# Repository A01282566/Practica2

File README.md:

# Practice 2. Developiong the PCB (Layout)

## Objectives

Develop the connection diagrams (layout) from the schematic diagram.

## Introduction

Microcontrollers are all around  he world. Each day, Microcontrollers, are more present in the many aspects of our lives: in our work, inside our houses, and in more. We can find them controlling small devices like cellphones, microwaves, washing machines, and televisions.

A microcontroller is one device or chip that is used to govern one or more processes. For example, the controller that regulates the room temperature of an air conditioner; it has a sensor that continuously measures the internal temperature and, when the preset limits are exceeded, it generates the necessary signals to adjust the temperature.

## State of the Art

### The practices and the PIC microcontroller

The main objective of this practices is to provide students the foundation to fully understand the operation of the PIC18F45K50 microcontroller. This will be achieved through 11 documents that will guide the reader to create their own electronic card or Printed Circuit Board (PCB) and to be able to program it; in order to, execute different functions.

The advantages of ta PIC microcontroller to others on the market, which is why it will be used throughout this manual, are as follows:

- Easy to operate.
- There is enough documentation to work with it and it’s easy to obtain it.
- The price is comparatively lower than its competitors.
- It has a high operating speed.
- Development tools are cheap and easy to use.
- There are a variety of hardware that can record, erase and check the behavior of PIC.
- Once you learn to handle a PIC, it will easier to handle any other models of microcontrollers.

### KiCad EDA Software

KiCad is an open source software suite for Electronic Design Automation (EDA). The programs handle Schematic Capture,
and PCB Layout with Gerber output. The suite runs on Windows, Linux and macOS and is licensed under GNU GPL v3. The
first release date was in 1992 by its original author, Jean-Pierre Charras, but is now currently under development by
the KiCad Developers Team. 

## Results

In this section, you must report the outcomes of the laboratory activities.

### Follow the next 'Project Configuration' Steps

1. In  the  same  project  from  practice  1,  click  on  the  icon ‘Assign PCB footprints to schematic symbols’.  By  doing  so,  you  will  be  able  to  watch  the  footprints associations in a list format. ***NOTE:*** *If a ***‘Confirmation’*** window pops to reassign all the components to a new library format, click ‘No.’*

2. Now it is time to add the corresponding libraries to the Cvpcbprogram.   Download from [here](./modules)  the modules   needed   for   the   project.   Click   on Preferences→Manage Footprint Libraries...and  in this  way  you  will  be  able  to  add  the  modules  from the folder  named  ‘modules.’  Click  on  ‘Project  Specific Libraries...’  tab,  then  click  on  the  button  ‘Browse Libraries...’ and search for the folder  where  you  save the modules. Select all the files and click ‘OK.’Fig.  1 shows the result of the added modules. NOTE:Your KiCad EDA Software must be in english to add the modules.

3. Once  that  is  done,  you  must  associate  the  list  of components  with  its  respective  footprint using Table  I for  guidance.  Be  sure  to  activate  the  option  ‘Filter footprints  list  by  library’ from  the Cvpcbtoolbar. To associate  the  components  showed  in  the middle  column,  double  click  with  their  corresponding footprint from the right column. ***NOTE:*** *Search  all  the  footprints  in  the*  ***‘user’*** *and * 
***‘discrete’*** * added libraries that should be found at the end of the list.*

4. Save   your modifications  by  clicking  **‘Apply,  Save Schematic & Continue,’ and then click ‘OK.’**
5. After that, you may close the Cvpcband go back to the EESchema (Schematic  Editor.)  Save  your  project  by clicking   on File→Save.   Close   the   editor   of   the Schematic and switch back to the **‘Project Manager.’**

6. Once you have the design of the circuit on the schematic, it is time to generate the **‘layout’** of our PCB  using the Netlist  file. On  the Project  Manager program  from KiCad, click on the icon **‘PCB layout editor’** . A new window will appear from the PCBNew. Click **‘Yes’** in the confirmation window.
7. On  the  toolbar  menu  from  the PCBNew click  on  the **‘Page  Settings  for  paper  size  and  texts’**
and modify the size settings to **‘USLetter 8.5x11in.’**

8. After  that,  it  will be  time  to  focus  more  on  design concepts.  You  may  do  so  by  opening  the
menu  of **‘Setup→Design Rules...’**. On   it,   some   final   design characteristics will appear with many millimeter values. Between   them,   you   should   find  the  **‘Clearance’** specification  which  is  the  smallest  spaces  that  it  must exist  between  the tracks  on the  PCB.  You  shall  set the value of this cell to 0.508 mm (0.020 inches.) Next, we set  a  value  of 1.200  mm  (0.047244 inches)on the  cell of **‘Track Width.’** 

9. Switch now to the ‘Global Design Rules’ tab and write, if needed, the minimum values for each an every one of the parameters on the ‘Minimum Allowed Values’ box. Click ‘OK.’

10. Time  to  import  the  Netlist  file.  Go  to  the  toolbar ‘Tools→Update  PCB  from  Schematic...’  and  then click on ‘Update  PCB.’ When  you  close  the  window all the components will appear on the screen.

11.Check in the ‘Layers Manager’ window (located at the right  part  of  your  screen) that all  the needed  boxes  are
checked, as shown:

11.Check in the ‘Layers Manager’ window (located at the right  part  of  your  screen) that all  the needed  boxes  are checke

12. Now you  have  to  define  the  limits  of  the  PCB.  First, highlight  the  ‘Edge.Cuts’  layer.  Then,  select  the  ‘Add  graphic lines’ tool and began to trace the original measures of your copper board (15x20 cm.) You must also define the  cutting  area;  do  not  forget  to  add  a  2.5  cm  margin around the board. To measure the lines, you can use the ‘Add dimension’ tool located on the right.

13. It is your turn to move all the components in the circuit in  order  to  avoid  any  track  intersection  inside  the working   area.   You   can   move   the   components   by positioning your mouse pointer above it and pressing the key [G]. All the components are connected to each other by a group of wires called ratsnest. Make sure that the icon  of  **‘Hide  board  ratsnest’** located  in  the toolbar of the left is highlighted.

14. Now you must link all the connections of you PCB. But before  that,  you  must  change  the  drawing  option  from the right toolbar from ‘Edge.Cuts’ to ‘B.Cu (PgDn)’ (B->Bottom, Cu->Copper.).

15. Start to connect your tracks to each and every one pin on the schematic by using the icon ‘Route Tracks’. Trace  all  the  routes  for  each  net  or  connection  in  your PCB design.

16. Once  your  are  done,  save  your  layout  File->Save  or using the command [Ctrl + S].

17. Your board must look like:

### Report
For this practice, modify only the Conclusion section. Commit an push the changes on the fork of this repository and add
upload the link on Canvas.

### File uploads
Commit and push the files with extensions .pro and .kicad_pcb created once you completed all the steps of the document in the repository.

### Demonstration
Screenshot the image of the complete schematic and upload it at the repository.

## Conclusion

In conclusion it can be said that with KidCad not only we can draw the schematic but also do the PCB layout of it. One problem that I had was that I couldn't draw the green connection lines at fisrt, but after I told my professor about it, we resolved it during tutoring. Also, one thing very difficult for me was to understand the white webs that are supposed to guide the conecctions, but later I realized that it was because I needed to rotate certain elements in order to see the lines clearer, as they were very confusing.
So, with this practice I discovered that those web lines are very helpful, so you don't have to be looking at the schematic all the time. And, I learned how to draw the copper lines to delimitate the area of the PCB.

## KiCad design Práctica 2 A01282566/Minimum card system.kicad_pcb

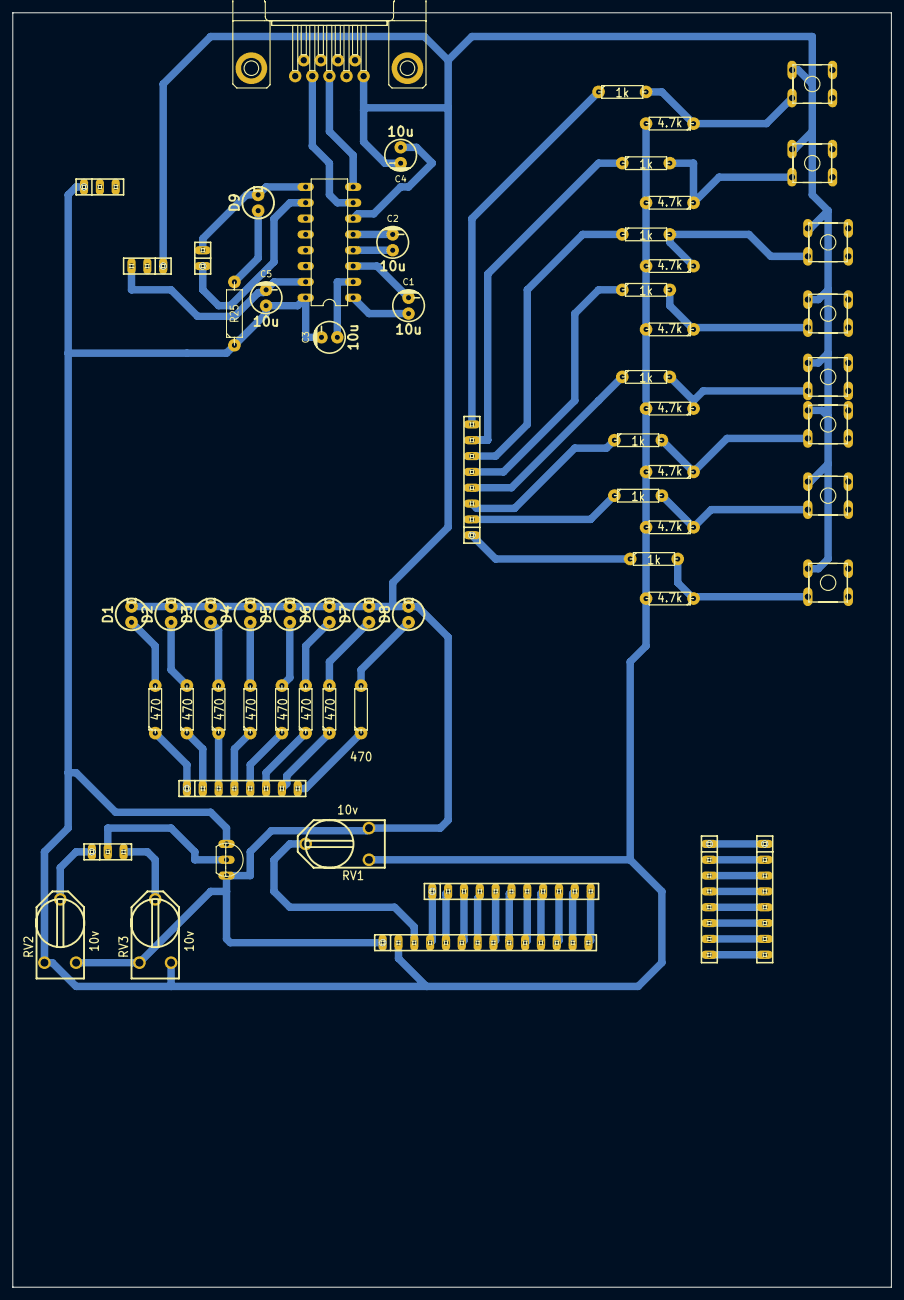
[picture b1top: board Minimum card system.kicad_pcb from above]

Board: 2 copper layers, 141.0 x 204.5 mm, 63 parts (0 on the bottom side), 68 nets.

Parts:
C1, C2, C3, C4, C5: 10u; Capacitor_elect
D1, D2, D3, D4, D5, D6, D7, D8, D9: LED; Led
JP1, JP2, JP7: PINHD-1X3; pinhead-1X03
JP3: PINHD-1X14; pinhead-1X14
JP4, JP5, JP8, JP9: PINHD-1X8; pinhead-1X08
JP6: PINHD-1X11; pinhead-1X11
JP10: PINHD-1X2; pinhead-1X02
R1, R2, R3, R4, R5, R6, R7, R8: 470; Resistor
R9, R10, R11, R12, R13, R14, R15, R16: 1k; Resistor
R17, R18, R19, R20, R21, R22, R23, R24: 4.7k; Resistor
R25: 470; Resistor_large
RV1, RV2, RV3: 10v; RV2X4
S1, S2, S3, S4, S5, S6, S7, S8: DTS-6
U1: MCP9700A
U2: MAX232; Maxim232
X1: F09HP; Conector_F09HP

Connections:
+5VA: C3.2, C5.1, JP1.1, JP1.2, JP1.3, JP3.2, R17.2, R18.2, R19.2, R20.2, R21.2, R22.2, R23.2, R24.2, R25.1, RV1.1, RV2.1, RV3.3, U1.1, U2.16
GNDA: C4.2, C5.2, D1.2, D2.2, D3.2, D4.2, D5.2, D6.2, D7.2, D8.2, JP2.1, JP2.2, JP2.3, JP3.1, RV1.3, RV2.3, RV3.1, S1.1, S2.1, S3.1, S4.1, S5.1, S6.1, S7.1, S8.1, U1.3, U2.15, X1.5
unnamed: C1.1, U2.1
unnamed: C1.2, U2.3
unnamed: C2.1, U2.4
unnamed: C2.2, U2.5
unnamed: C3.1, U2.2
unnamed: C4.1, U2.6
unnamed: D1.1, R1.2
unnamed: D2.1, R2.2
unnamed: D3.1, R3.2
unnamed: D4.1, R4.2
unnamed: D5.1, R5.2
unnamed: D6.1, R6.2
unnamed: D7.1, R7.2
unnamed: D8.1, R8.2
unnamed: D9.1, R25.2
unnamed: D9.2, JP10.2, U2.9
unnamed: JP3.3, RV1.2
unnamed: JP3.4, JP6.1
unnamed: JP3.5, JP6.2
unnamed: JP3.6, JP6.3
unnamed: JP3.7, JP6.4
unnamed: JP3.8, JP6.5
unnamed: JP3.9, JP6.6
unnamed: JP3.10, JP6.7
unnamed: JP3.11, JP6.8
unnamed: JP3.12, JP6.9
unnamed: JP3.13, JP6.10
unnamed: JP3.14, JP6.11
unnamed: JP4.1, JP5.1
unnamed: JP4.2, JP5.2
unnamed: JP4.3, JP5.3
unnamed: JP4.4, JP5.4
unnamed: JP4.5, JP5.5
unnamed: JP4.6, JP5.6
unnamed: JP4.7, JP5.7
unnamed: JP4.8, JP5.8
unnamed: JP7.1, RV2.2
unnamed: JP7.2, U1.2
unnamed: JP7.3, RV3.2
unnamed: JP8.1, R1.1
unnamed: JP8.2, R2.1
unnamed: JP8.3, R3.1
unnamed: JP8.4, R4.1
unnamed: JP8.5, R5.1
unnamed: JP8.6, R6.1
unnamed: JP8.7, R7.1
unnamed: JP8.8, R8.1
unnamed: JP9.1, R9.1
unnamed: JP9.2, R10.1
unnamed: JP9.3, R11.1
unnamed: JP9.4, R12.1
unnamed: JP9.5, R13.1
unnamed: JP9.6, R14.1
unnamed: JP9.7, R15.1
unnamed: JP9.8, R16.1
unnamed: JP10.1, U2.10
unnamed: R10.2, R18.1, S2.3
unnamed: R11.2, R19.1, S3.3
unnamed: R12.2, R20.1, S4.3
unnamed: R13.2, R21.1, S5.3
unnamed: R14.2, R22.1, S6.3
unnamed: R15.2, R23.1, S7.3
unnamed: R16.2, R24.1, S8.3
unnamed: R9.2, R17.1, S1.3
unnamed: U2.7, X1.2
unnamed: U2.8, X1.3
